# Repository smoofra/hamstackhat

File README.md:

hamstackHAT
==========

This is a raspberry pi HAT board for interfacing to a
[hamstack Series 200](http://www.hamstack.com/repeatercontroller.html)
repeater controller.

It is compatible with raspberries with the 40 pin header, such as the B+.

The hamstack cpu board has a db25 gpio connector with 8 digital out pins and 8
digital in pins.  These are connected to the 16 general purpose gpio pins on the
pi.  The UART, SPI, and I2C pins are left unused.  The hamstack's analog inputs
are unused.

The pin assignments are:

|Raspberry       |Hamstack       |
|----------------|---------------|
|GPIO26          |DIGITAL IN 13  |
|GPIO19          |DIGITAL IN 12  |
|GPIO13          |DIGITAL IN 24  |
|GPIO6           |DIGITAL IN 11  |
|GPIO5           |DIGITAL IN 23  |
|GPIO22          |DIGITAL IN 10  |
|GPIO27          |DIGITAL IN 22  |
|GPIO17          |DIGITAL IN 9   |
|GPIO18          |DIGITAL OUT 5  |
|GPIO23          |DIGITAL OUT 7  |
|GPIO24          |DIGITAL OUT 6  |
|GPIO25          |DIGITAL OUT 8  |
|GPIO12          |DIGITAL OUT 18 |
|GPIO16          |DIGITAL OUT 19 |
|GPIO20          |DIGITAL OUT 20 |
|GPIO21          |DIGITAL OUT 21 |

The hamstack also has a RS232 control interface.  To interface that just use any
USB to RS232 adapter cable.

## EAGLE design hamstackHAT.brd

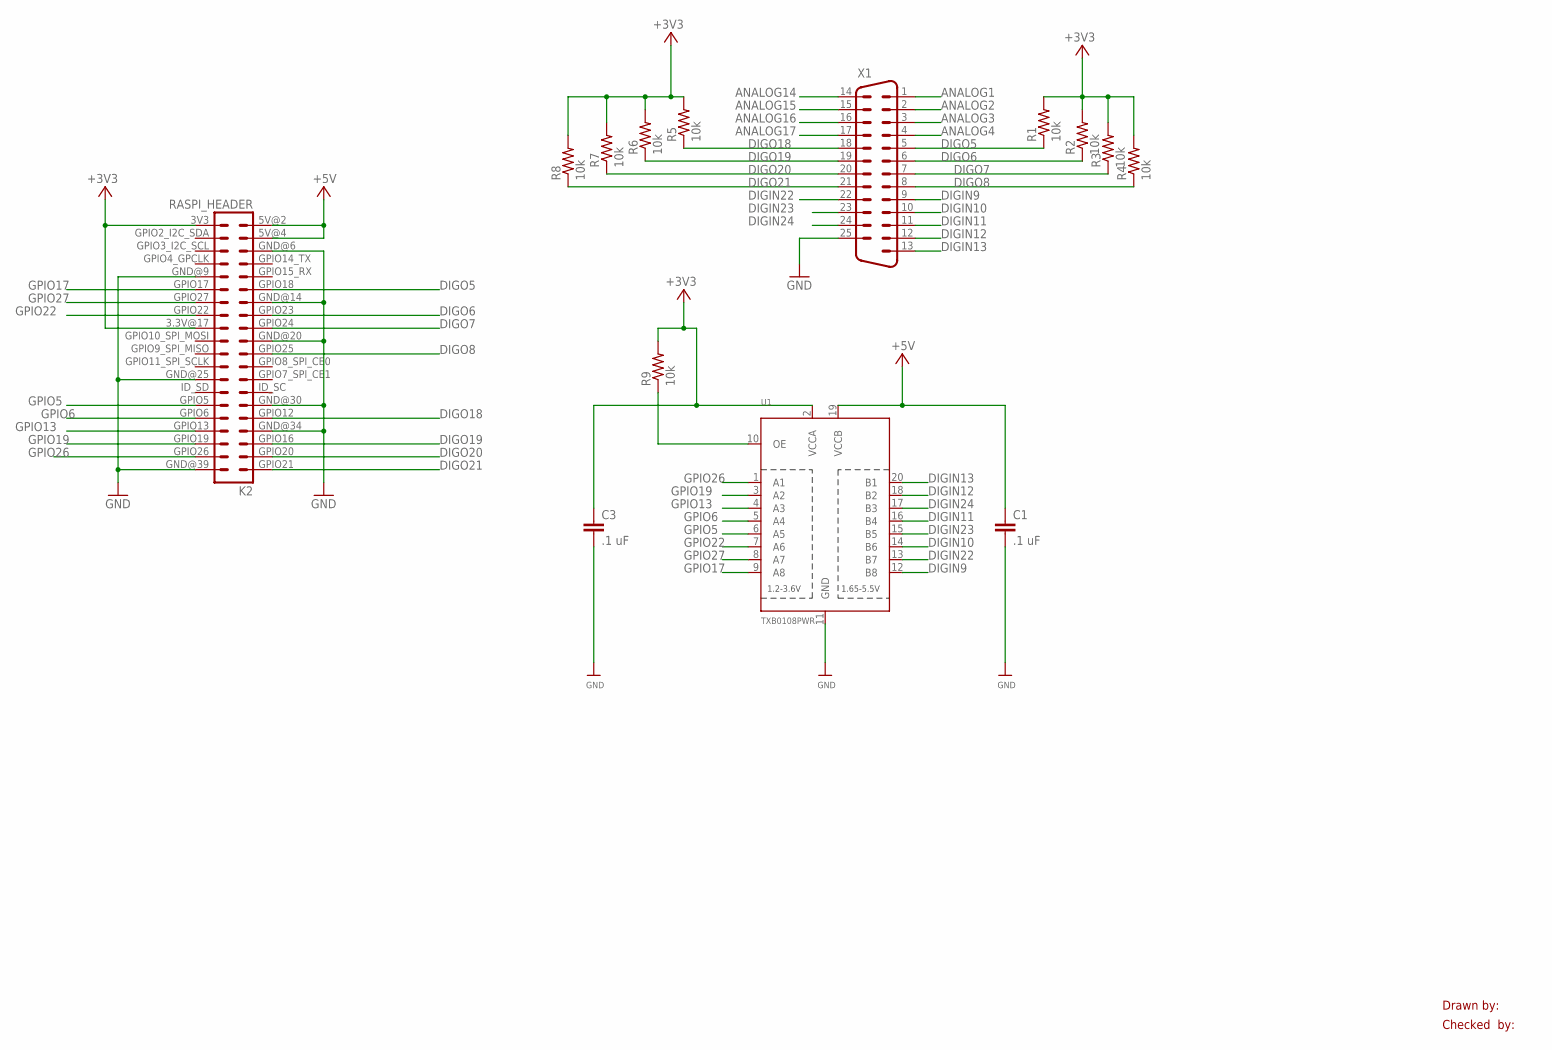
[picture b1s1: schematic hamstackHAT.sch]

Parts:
C1, C3: .1 uF; CAP-PTH-SMALL-KIT
K2: RASPI_HEADER
R1, R2, R3, R4, R5, R6, R7, R8, R9: 10k; 0207/10
U1: TXB0108PWR; TSSOP20
X1: M25HP

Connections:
+3V3: C3.1, K2.3.3V@17 (17), K2.3V3 (1), R1.2, R2.2, R3.2, R4.2, R5.2, R6.2, R7.2, R8.2, R9.2, U1.2 (VCCA)
+5V: C1.1, K2.5V@2 (2), K2.5V@4 (4), U1.19 (VCCB)
ANALOG1: X1.1
ANALOG2: X1.2
ANALOG3: X1.3
ANALOG4: X1.4
ANALOG14: X1.14
ANALOG15: X1.15
ANALOG16: X1.16
ANALOG17: X1.17
DIGIN9: U1.12 (B8), X1.9
DIGIN10: U1.14 (B6), X1.10
DIGIN11: U1.16 (B4), X1.11
DIGIN12: U1.18 (B2), X1.12
DIGIN13: U1.20 (B1), X1.13
DIGIN22: U1.13 (B7), X1.22
DIGIN23: U1.15 (B5), X1.23
DIGIN24: U1.17 (B3), X1.24
DIGO5: K2.GPIO18 (12), R1.1, X1.5
DIGO6: K2.GPIO23 (16), R2.1, X1.6
DIGO7: K2.GPIO24 (18), R3.1, X1.7
DIGO8: K2.GPIO25 (22), R4.1, X1.8
DIGO18: K2.GPIO12 (32), R5.1, X1.18
DIGO19: K2.GPIO16 (36), R6.1, X1.19
DIGO20: K2.GPIO20 (38), R7.1, X1.20
DIGO21: K2.GPIO21, R8.1, X1.21
GND: C1.2, C3.2, K2.GND@6 (6), K2.GND@9 (9), K2.GND@14 (14), K2.GND@20 (20), K2.GND@25 (25), K2.GND@30 (30), K2.GND@34 (34), K2.GND@39 (39), U1.11 (GND), X1.25
GPIO5: K2.GPIO5 (29), U1.6 (A5)
GPIO6: K2.GPIO6 (31), U1.5 (A4)
GPIO13: K2.GPIO13 (33), U1.4 (A3)
GPIO17: K2.GPIO17 (11), U1.9 (A8)
GPIO19: K2.GPIO19 (35), U1.3 (A2)
GPIO22: K2.GPIO22 (15), U1.7 (A6)
GPIO26: K2.GPIO26 (37), U1.1 (A1)
GPIO27: K2.GPIO27 (13), U1.8 (A7)
unnamed: R9.1, U1.10 (OE)

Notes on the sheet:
Drawn by:
Checked by:

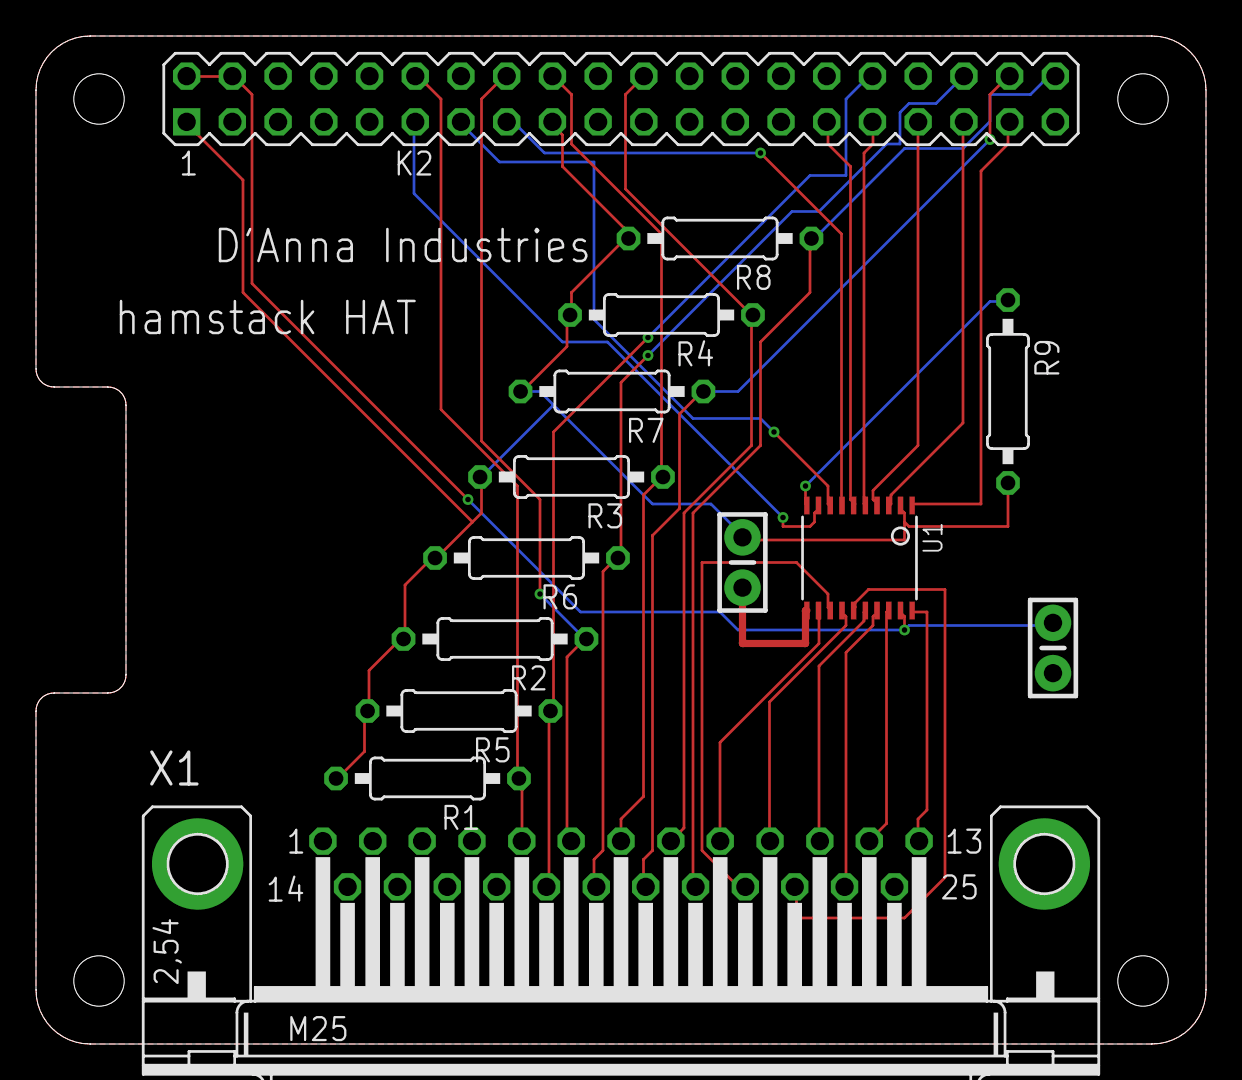
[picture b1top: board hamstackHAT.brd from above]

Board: 2 copper layers, 65.0 x 56.0 mm, 14 parts (0 on the bottom side), 28 nets.

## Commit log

2015-04-03 downloaded template from the internet
2015-04-03 imported into project
2015-04-03 add pin labels to raspi header
2015-04-03 add db15 and labeled nets
2015-04-03 add pullups
2015-04-03 hook up digo pins to gpios
2015-04-03 route
2015-04-03 clean up traces
2015-04-03 silkscreen
2015-04-03 add level shifter
2015-04-03 re-route
2015-04-03 add hamstack HAT label
2015-04-03 rename files
2015-04-03 add readme
2015-04-04 re-arange everythign to imporove routing
2015-04-04 readme
2015-04-04 pin table
2015-04-04 typo
2015-04-04 tidy up schematic for letter paper
2015-04-04 add images

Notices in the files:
parts and their libraries:
SparkFun-Capacitors: Licensing: Creative Commons ShareAlike 4.0 International - https://creativecommons.org/licenses/by-sa/4.0
